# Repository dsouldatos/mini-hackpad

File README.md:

# Mini Keyboard 🎛️

A compact custom-designed mini keyboard featuring **4 mechanical-style switches** and a **rotary encoder**. The keyboard is designed to be small, simple, and customizable while keeping a clean modern look.

## ✨ Features

* 4 customizable switches
* 1 rotary encoder
* Custom-designed PCB
* Custom 3D-printed case
* Compact and portable design
* LED lighting
* Designed in CAD
* Easy to customize and modify

## 🛠️ BOM
* Custom PCB
*  Custom 3D-printed enclosure
* 1 Seeeduino XIAO microcontroller
* 4 MX switches
* 1 rotary encoder
* 7 SK6812 MINI-E LEDs
* 1 Soldering Iron
* Printing Legion Grant
* Hackpad PCB Grant
## 📁 Project Files

* `PCB/` – PCB design files

* `CAD/` – 3D models and enclosure

* `Firmware/` – Keyboard firmware

* `README.md` – Project information

## 🚀 Project Status

The PCB and enclosure have been designed
## 📜 License

This project is open-source. You are welcome to use, modify, and improve the design.

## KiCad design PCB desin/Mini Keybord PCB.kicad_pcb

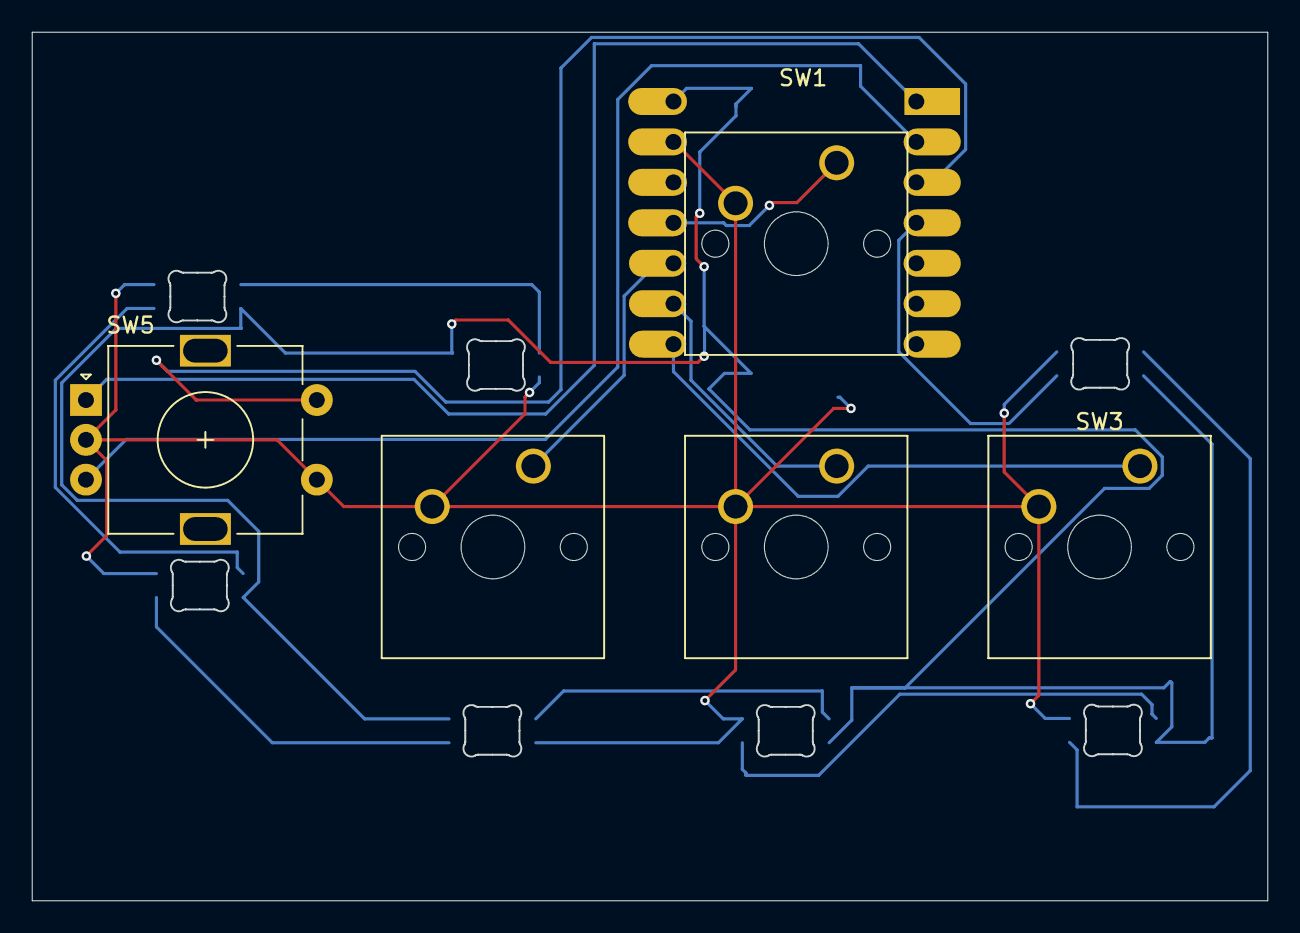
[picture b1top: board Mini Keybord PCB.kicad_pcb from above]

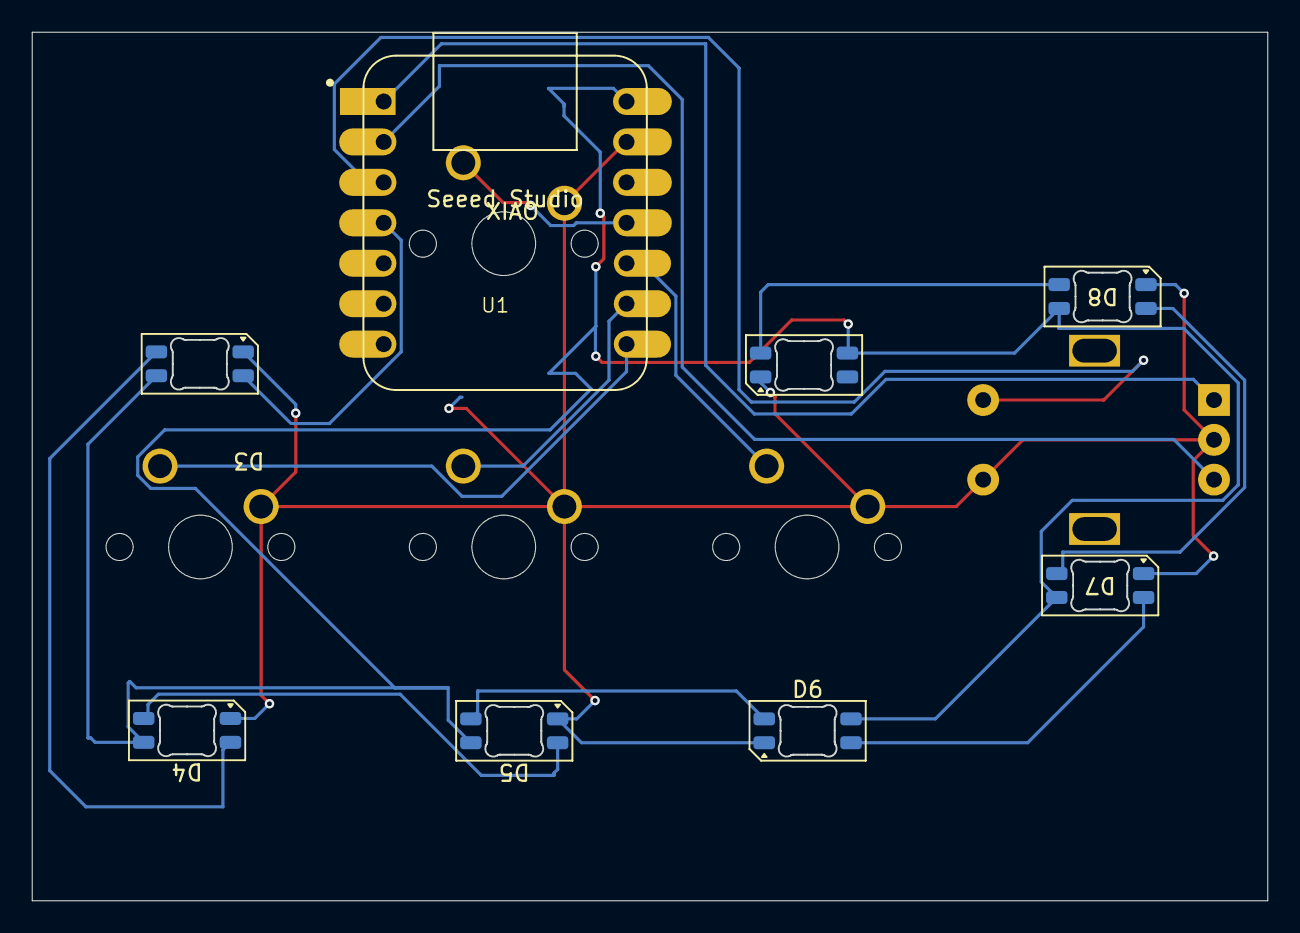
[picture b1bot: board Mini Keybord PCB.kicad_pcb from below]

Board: 2 copper layers, 77.6 x 54.5 mm, 13 parts (8 on the bottom side), 16 nets.

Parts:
D3, D4, D5, D6, D7, D8, D9: SK6812MINI-E; LED_SK6812MINI-E_3.2x2.8mm_P1.5mm_ReverseMount
SW1, SW2, SW3, SW4: SW_Push; SW_Cherry_MX_1.00u_PCB
SW5: RotaryEncoder_Switch; RotaryEncoder_Alps_EC11E-Switch_Vertical_H20mm
U1: MOUDLE-SEEEDUINO-XIAO; XIAO-Generic-Hybrid-14P-2.54-21X17.8MM

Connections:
GND: D3.1 (VSS), D4.1 (VSS), D5.1 (VSS), D6.1 (VSS), D7.1 (VSS), D8.1 (VSS), D9.1 (VSS), SW1.2, SW2.2, SW3.2, SW4.2, SW5.C, SW5.S1, U1.13 (GND)
unnamed: D3.2 (DIN), U1.4 (PA11_A3_D3)
unnamed: D3.4 (DOUT), D4.2 (DIN)
unnamed: D3.3 (VDD), D4.3 (VDD), D5.3 (VDD), D6.3 (VDD), D7.3 (VDD), D8.3 (VDD), D9.3 (VDD), U1.14 (5V)
unnamed: D4.4 (DOUT), D5.2 (DIN)
unnamed: D5.4 (DOUT), D6.2 (DIN)
unnamed: D6.4 (DOUT), D7.2 (DIN)
unnamed: D7.4 (DOUT), D8.2 (DIN)
unnamed: D8.4 (DOUT), D9.2 (DIN)
unnamed: SW5.A, U1.1 (PA02_A0_D0)
unnamed: SW5.B, U1.2 (PA4_A1_D1)
unnamed: SW4.1, U1.10 (PA5_A9_D9_MISO)
unnamed: SW1.1, U1.11 (PA6_A10_D10_MOSI)
unnamed: SW2.1, U1.9 (PA7_A8_D8_SCK)
unnamed: SW5.S2, U1.3 (PA10_A2_D2)
unnamed: SW3.1, U1.8 (PB09_A7_D7_RX)
